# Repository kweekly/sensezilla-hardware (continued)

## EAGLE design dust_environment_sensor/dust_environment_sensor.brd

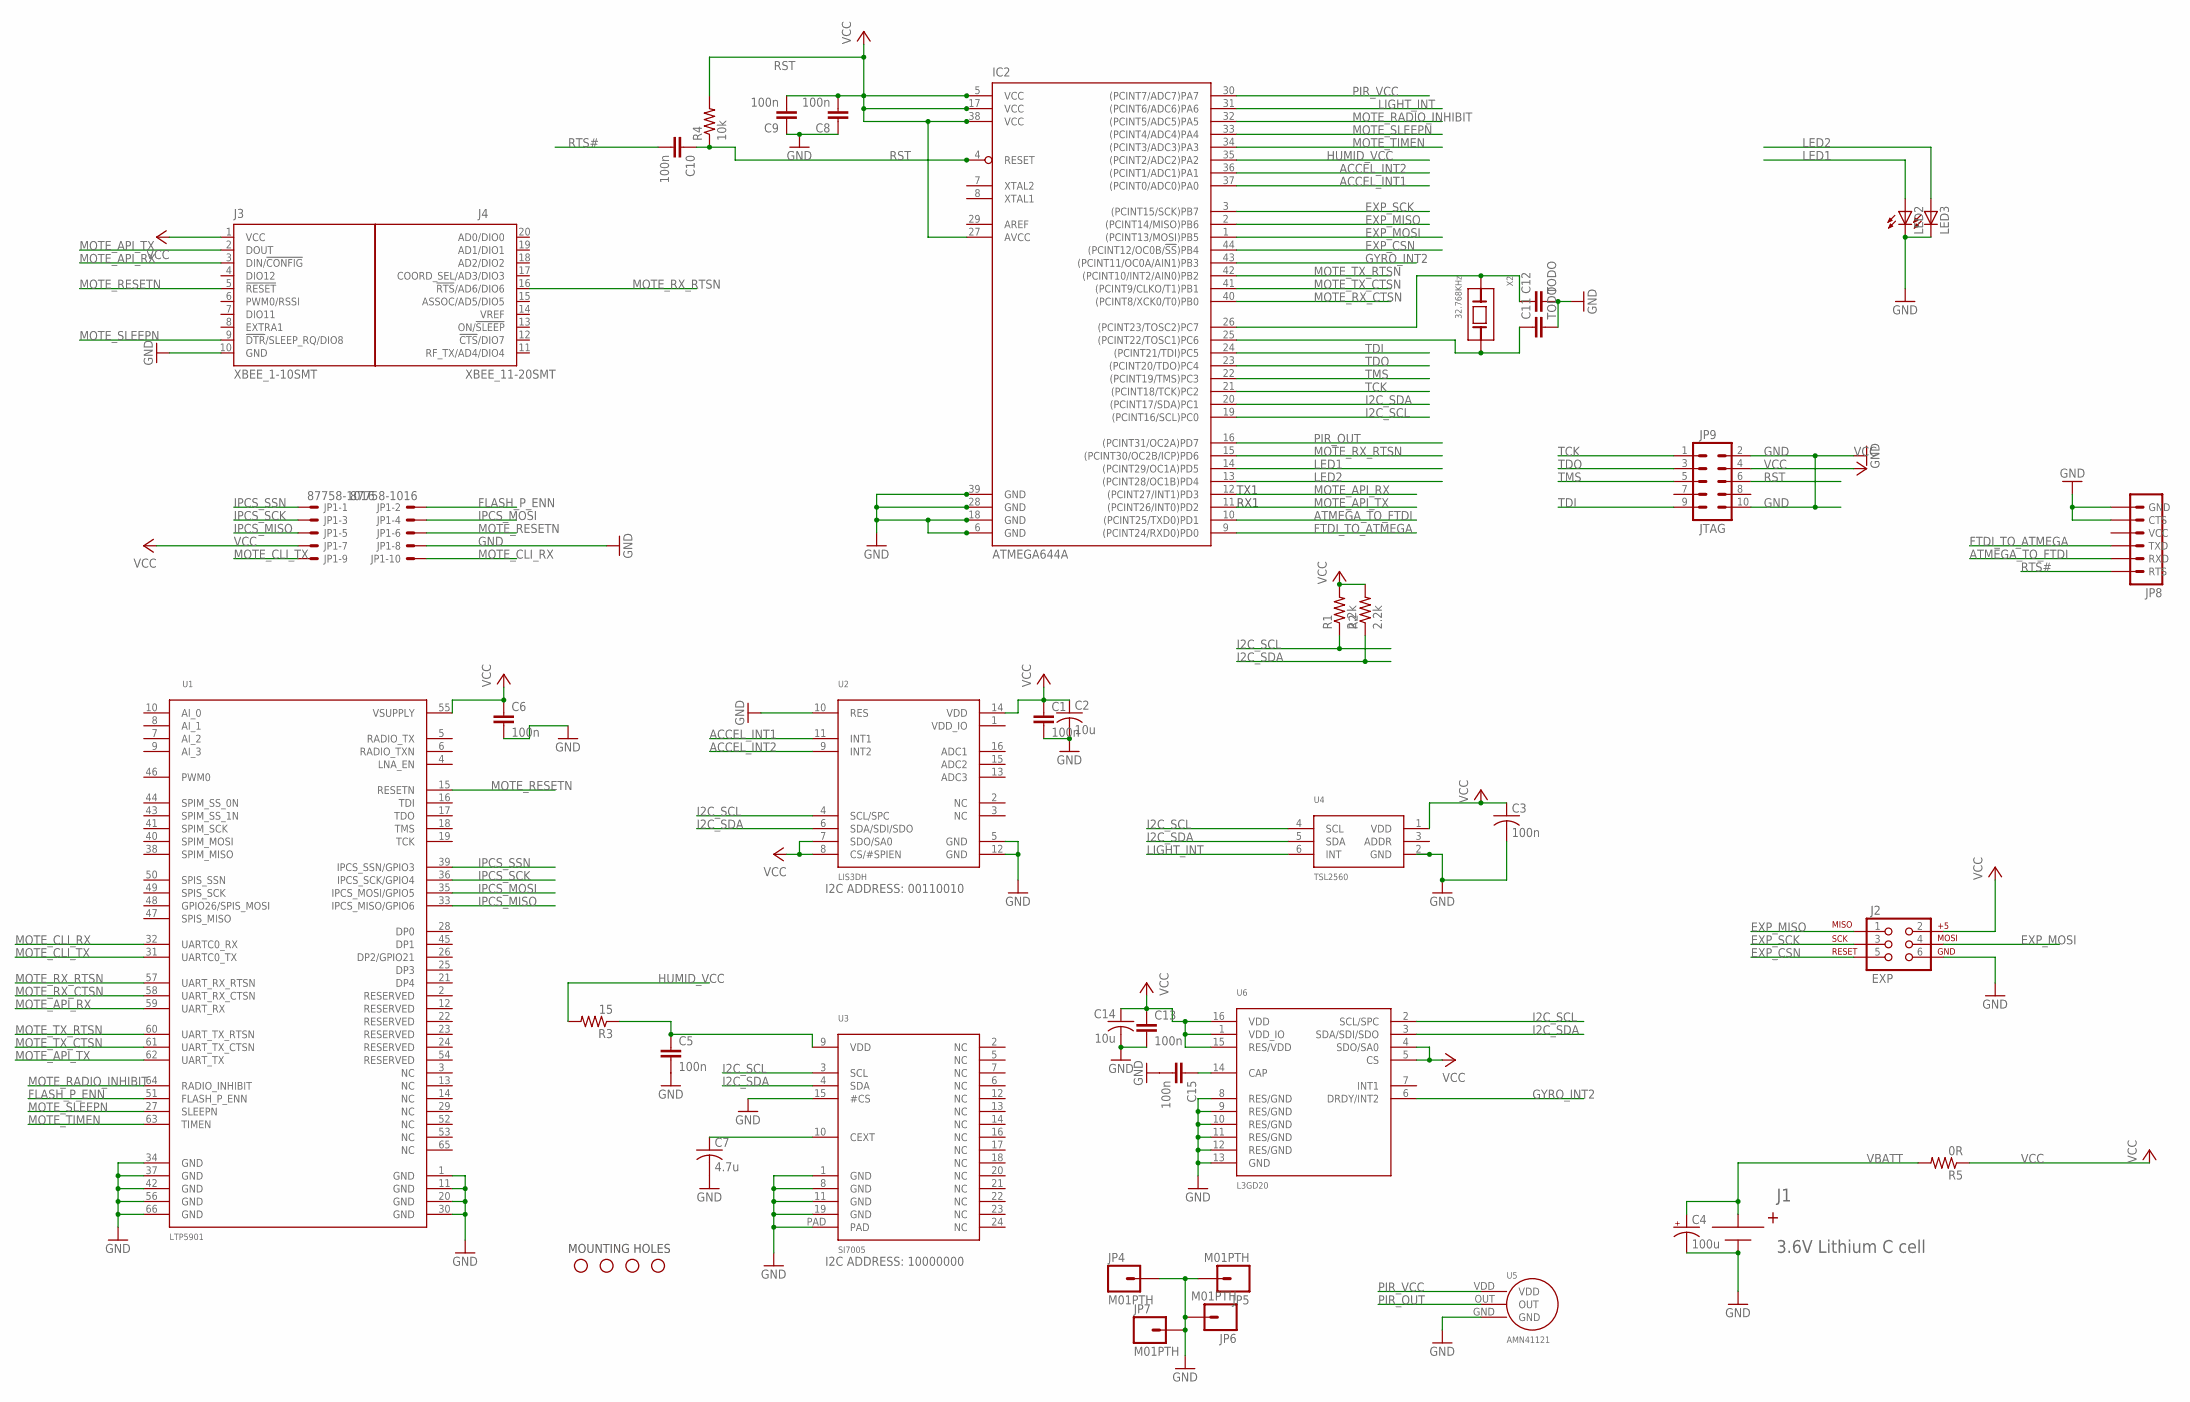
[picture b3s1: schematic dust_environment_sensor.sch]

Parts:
C1, C3, C5, C6, C8, C9, C10, C13, C15: 100n; C0603
C2, C14: 10u; C0603
C4: 100u; EIA3216-KIT
C7: 4.7u; C0603
C11, C12: TODO; C0603
IC2: ATMEGA644A; TQFP44
J1: 3.6V Lithium C cell; BX0036
J2: EXP; 2X3
J3: XBEE_1-10SMT; XBEE_1-10_SMT
J4: XBEE_11-20SMT; XBEE_11-20_SMT
JP1: 87758-1016
JP4, JP5, JP6, JP7: M01PTH; 1X01
JP8: FTDI_CABLESIP; 1X06
JP9: JTAG; AVR_ICSP
LED2, LED3: LEDCHIPLED_0805; CHIPLED_0805
R1, R2: 2.2k; R0603
R3: 15; R0603
R4: 10k; R0603
R5: 0R; R0603
STANDOFF1, STANDOFF2, STANDOFF3, STANDOFF4: STAND-OFF
U1: LTP5901; LTP5901_MODULE
U2: LIS3DH; LGA16_ST
U3: SI7005; QFN24_SILICON_LABS
U4: TSL2560; CL6_TAOS
U5: AMN41121
U6: L3GD20; LGA16_4X4_ST
X2: 32.768KHz; ABS07

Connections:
ACCEL_INT1: IC2.37 ((PCINT0/ADC0)PA0), U2.11 (INT1)
ACCEL_INT2: IC2.36 ((PCINT1/ADC1)PA1), U2.9 (INT2)
ATMEGA_TO_FTDI: IC2.10 ((PCINT25/TXD0)PD1), JP8.5 (RXD)
EXP_CSN: IC2.44 ((PCINT12/OC0B/!SS!)PB4), J2.5
EXP_MISO: IC2.2 ((PCINT14/MISO)PB6), J2.1
EXP_MOSI: IC2.1 ((PCINT13/MOSI)PB5), J2.4
EXP_SCK: IC2.3 ((PCINT15/SCK)PB7), J2.3
FLASH_P_ENN: JP1.2, U1.51 (FLASH_P_ENN)
FTDI_TO_ATMEGA: IC2.9 ((PCINT24/RXD0)PD0), JP8.4 (TXD)
GND: C1.2, C2.2, C3.2, C4.C (-), C5.2, C6.2, C7.2, C8.1, C9.1, C11.2, C12.2, C13.2, C14.2, C15.2, IC2.6 (GND), IC2.18 (GND), IC2.28 (GND), IC2.39 (GND), J1.NEG, J2.6, J3.10 (GND), JP1.8, JP4.1, JP5.1, JP6.1, JP7.1, JP8.1 (GND), JP8.2 (CTS), JP9.2, JP9.10, LED2.C, LED3.C, U1.1 (GND), U1.11 (GND), U1.20 (GND), U1.30 (GND), U1.34 (GND), U1.37 (GND), U1.42 (GND), U1.56 (GND), U1.66 (GND), U2.5 (GND), U2.10 (RES), U2.12 (GND), U3.1 (GND), U3.8 (GND), U3.11 (GND), U3.15 (#CS), U3.19 (GND), U3.PAD, U4.2 (GND), U5.GND, U6.8 (RES/GND), U6.9 (RES/GND), U6.10 (RES/GND), U6.11 (RES/GND), U6.12 (RES/GND), U6.13 (GND)
GYRO_INT2: IC2.43 ((PCINT11/OC0A/AIN1)PB3), U6.6 (DRDY/INT2)
HUMID_VCC: IC2.35 ((PCINT2/ADC2)PA2), R3.2
I2C_SCL: IC2.19 ((PCINT16/SCL)PC0), R1.1, U2.4 (SCL/SPC), U3.3 (SCL), U4.4 (SCL), U6.2 (SCL/SPC)
I2C_SDA: IC2.20 ((PCINT17/SDA)PC1), R2.1, U2.6 (SDA/SDI/SDO), U3.4 (SDA), U4.5 (SDA), U6.3 (SDA/SDI/SDO)
IPCS_MISO: JP1.5, U1.33 (IPCS_MISO/GPIO6)
IPCS_MOSI: JP1.4, U1.35 (IPCS_MOSI/GPIO5)
IPCS_SCK: JP1.3, U1.36 (IPCS_SCK/GPIO4)
IPCS_SSN: JP1.1, U1.39 (IPCS_SSN/GPIO3)
LED1: IC2.14 ((PCINT29/OC1A)PD5), LED2.A
LED2: IC2.13 ((PCINT28/OC1B)PD4), LED3.A
LIGHT_INT: IC2.31 ((PCINT6/ADC6)PA6), U4.6 (INT)
MOTE_API_RX: IC2.12 ((PCINT27/INT1)PD3), J3.3 (DIN/!CONFIG), U1.59 (UART_RX)
MOTE_API_TX: IC2.11 ((PCINT26/INT0)PD2), J3.2 (DOUT), U1.62 (UART_TX)
MOTE_CLI_RX: JP1.10, U1.32 (UARTC0_RX)
MOTE_CLI_TX: JP1.9, U1.31 (UARTC0_TX)
MOTE_RADIO_INHIBIT: IC2.32 ((PCINT5/ADC5)PA5), U1.64 (RADIO_INHIBIT)
MOTE_RESETN: J3.5 (!RESET), JP1.6, U1.15 (RESETN)
MOTE_RX_CTSN: IC2.40 ((PCINT8/XCK0/T0)PB0), U1.58 (UART_RX_CTSN)
MOTE_RX_RTSN: IC2.15 ((PCINT30/OC2B/ICP)PD6), J4.16 (!RTS!/AD6/DIO6), U1.57 (UART_RX_RTSN)
MOTE_SLEEPN: IC2.33 ((PCINT4/ADC4)PA4), J3.9 (!DTR!/SLEEP_RQ/DIO8), U1.27 (SLEEPN)
MOTE_TIMEN: IC2.34 ((PCINT3/ADC3)PA3), U1.63 (TIMEN)
MOTE_TX_CTSN: IC2.41 ((PCINT9/CLKO/T1)PB1), U1.61 (UART_TX_CTSN)
MOTE_TX_RTSN: IC2.42 ((PCINT10/INT2/AIN0)PB2), U1.60 (UART_TX_RTSN)
unnamed: C7.1, U3.10 (CEXT)
unnamed: C15.1, U6.14 (CAP)
unnamed: C5.1, R3.1, U3.9 (VDD)
unnamed: C11.1, IC2.25 ((PCINT22/TOSC1)PC6), X2.2 (B)
unnamed: C12.1, IC2.26 ((PCINT23/TOSC2)PC7), X2.1 (A)
PIR_OUT: IC2.16 ((PCINT31/OC2A)PD7), U5.OUT
PIR_VCC: IC2.30 ((PCINT7/ADC7)PA7), U5.VDD
RST: C10.1, IC2.4 (RESET), JP9.6, R4.1
RTS#: C10.2, JP8.6 (RTS)
TCK: IC2.21 ((PCINT18/TCK)PC2), JP9.1
TDI: IC2.24 ((PCINT21/TDI)PC5), JP9.9
TDO: IC2.23 ((PCINT20/TDO)PC4), JP9.3
TMS: IC2.22 ((PCINT19/TMS)PC3), JP9.5
VBATT: C4.A (+), J1.POS, R5.2
VCC: C1.1, C2.1, C3.1, C6.1, C8.2, C9.2, C13.1, C14.1, IC2.5 (VCC), IC2.17 (VCC), IC2.27 (AVCC), IC2.38 (VCC), J2.2, J3.1 (VCC), JP1.7, JP9.4, R1.2, R2.2, R4.2, R5.1, U1.55 (VSUPPLY), U2.7 (SDO/SA0), U2.8 (CS/#SPIEN), U2.14 (VDD), U4.1 (VDD), U6.1 (VDD_IO), U6.4 (SDO/SA0), U6.5 (CS), U6.15 (RES/VDD), U6.16 (VDD)

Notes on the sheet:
I2C ADDRESS: 00110010
MOUNTING HOLES
I2C ADDRESS: 10000000
TX1
RX1

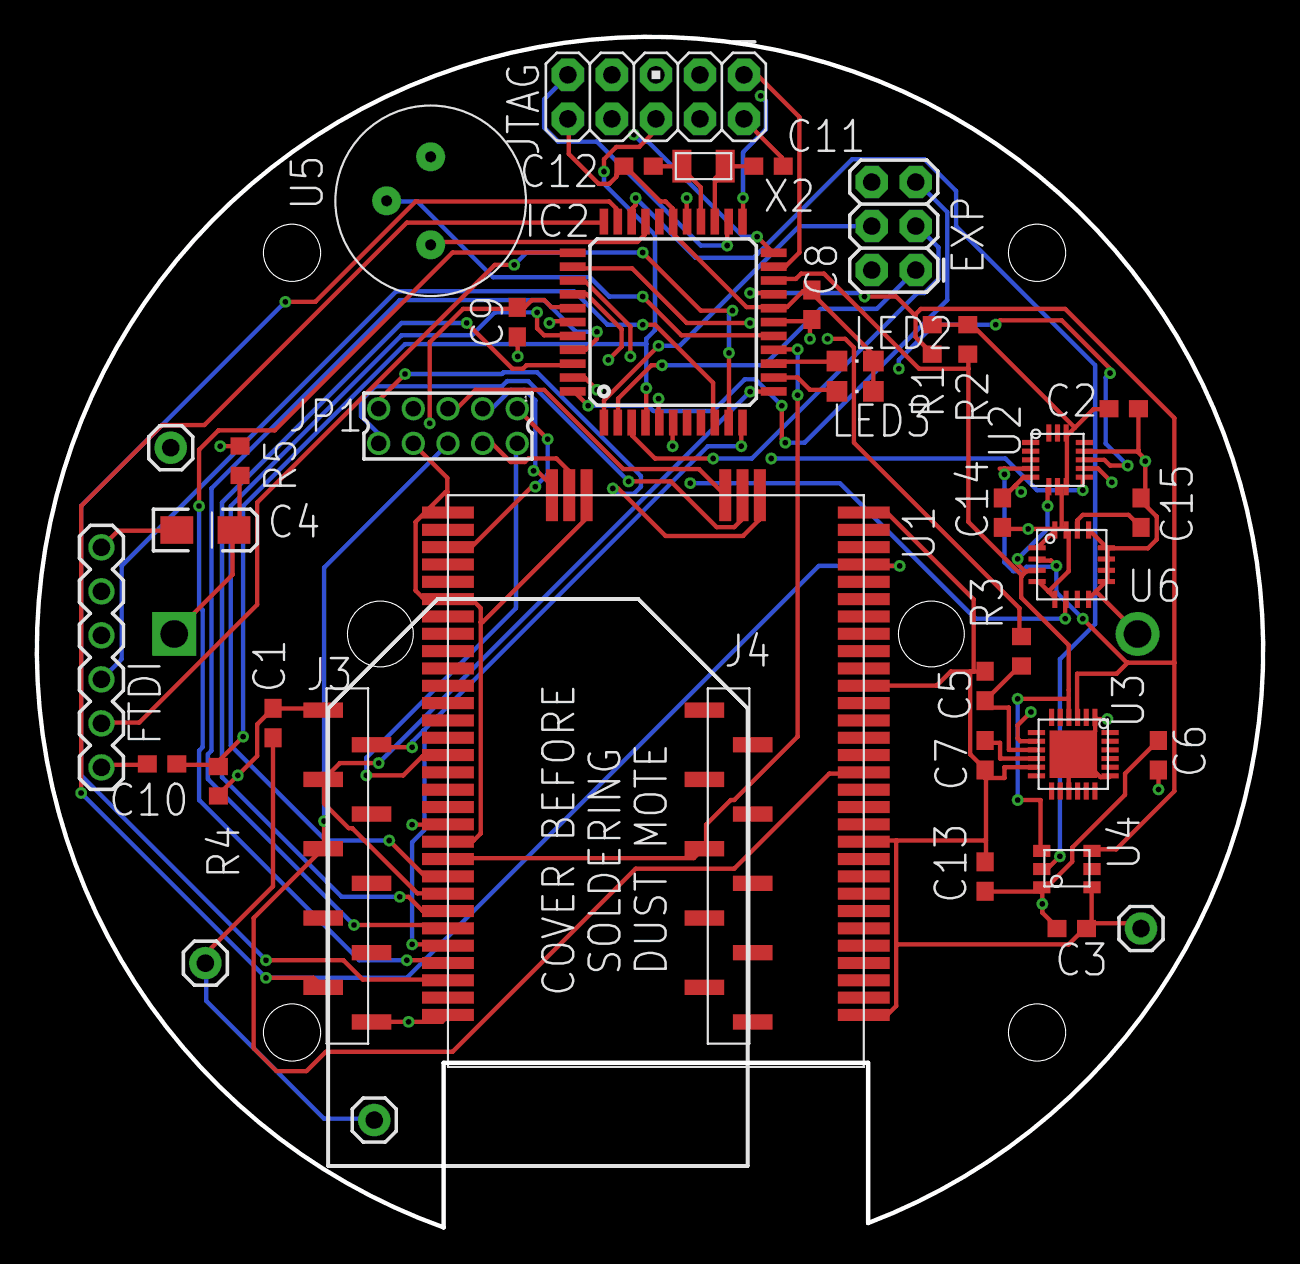
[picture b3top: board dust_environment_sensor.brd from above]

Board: 4 copper layers, 70.8 x 68.7 mm, 45 parts (1 on the bottom side), 48 nets.

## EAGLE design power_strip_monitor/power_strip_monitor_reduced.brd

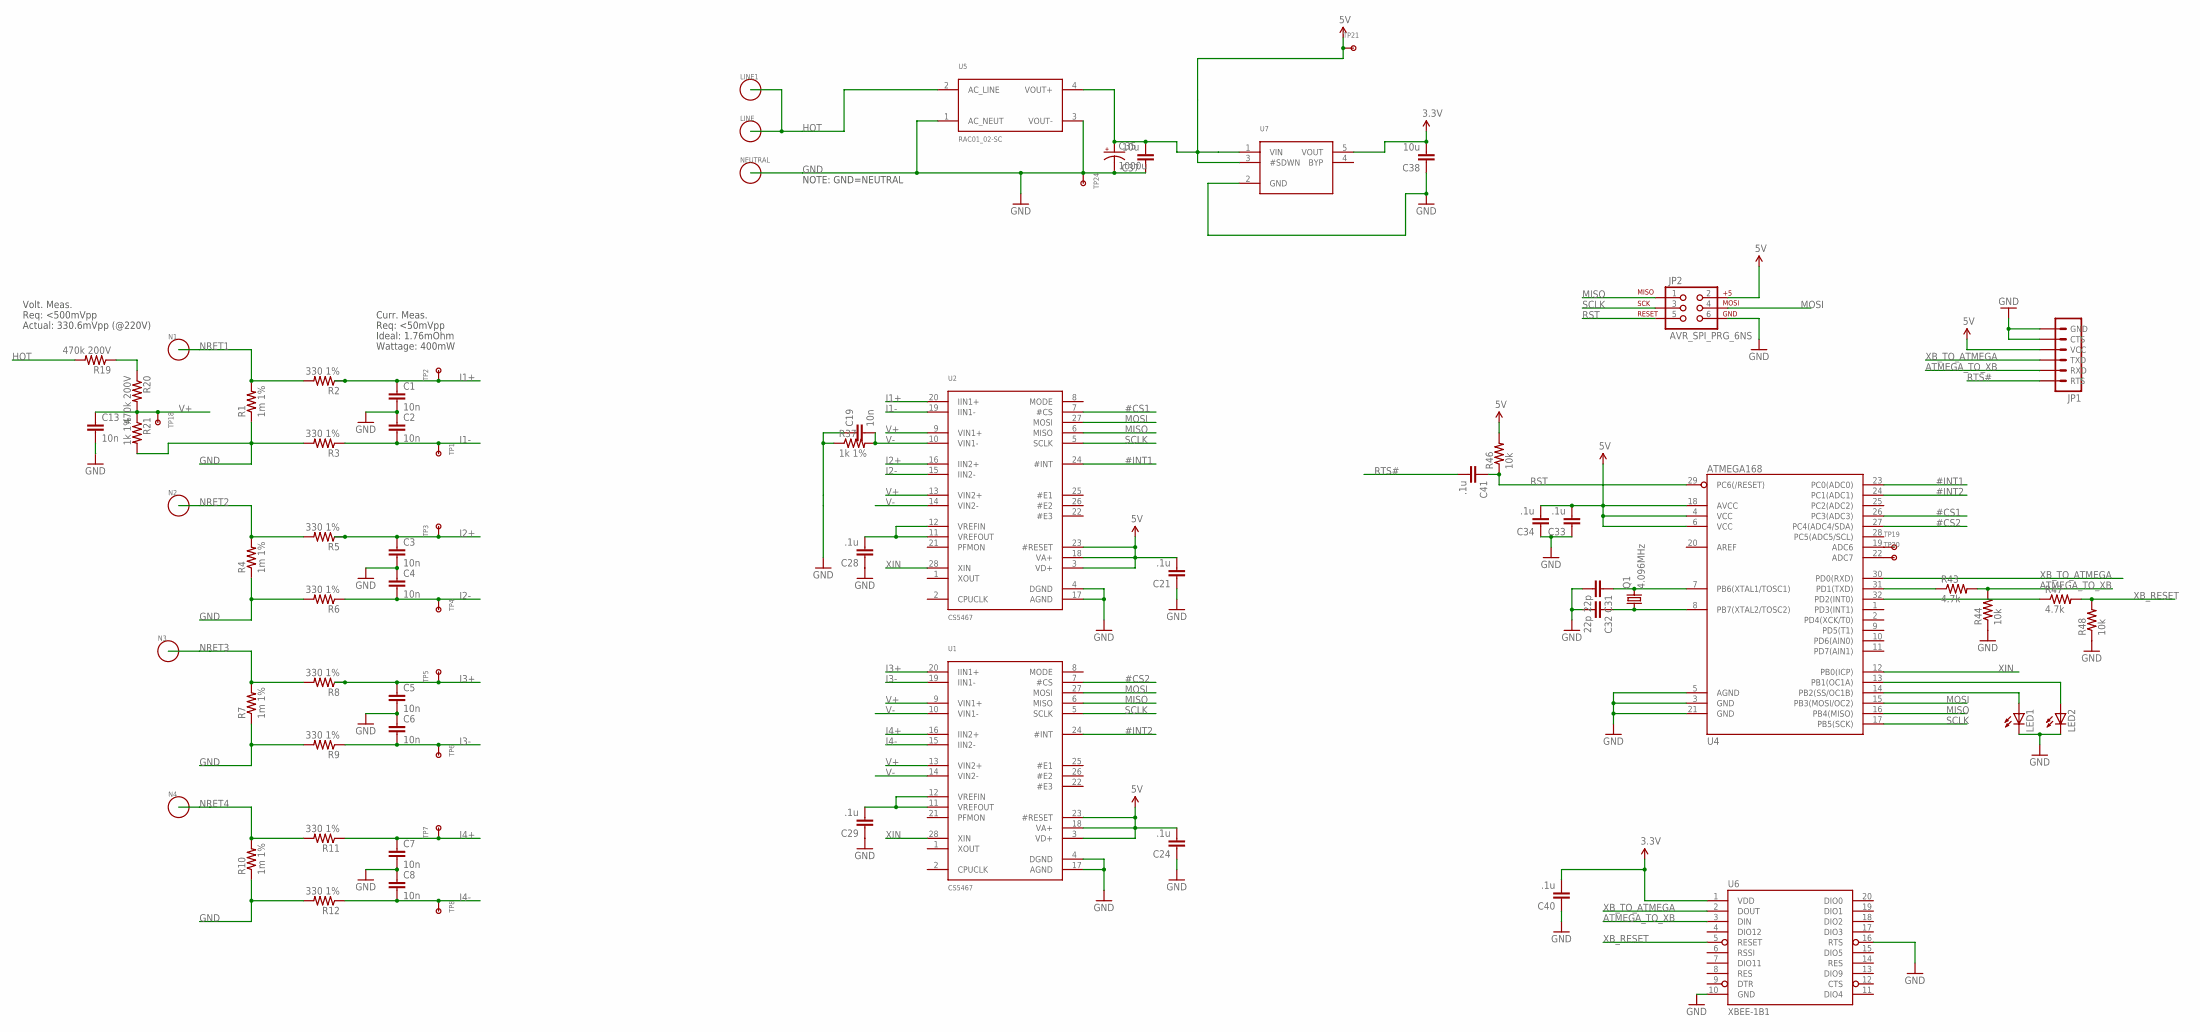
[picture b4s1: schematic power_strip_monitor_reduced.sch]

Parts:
C1, C2, C3, C4, C5, C6, C7, C8, C13, C19: 10n; 0603
C21, C24, C28, C29, C33, C34, C40, C41: .1u; 0603
C31, C32: 22p; 0603
C35: 1000u; PANASONIC_G
C37, C38: 10u; 0603
JP1: FTDI_CABLESIP; 1X06
JP2: AVR_SPI_PRG_6NS; 2X3-NS
LED1, LED2: LEDCHIPLED_0805; CHIPLED_0805
LINE, LINE1: 1P_HOLE; 14GAUGE_HOLE
N1, N2, N3, N4: 1P_HOLE; 14GAUGE_HOLE
NEUTRAL: 1P_HOLE; 14GAUGE_HOLE
Q1: 4.096MHz; HC49UP
R1, R4, R7, R10: 1m 1%; R2512
R2, R3, R5, R6, R8, R9, R11, R12: 330 1%; 0603
R19, R20: 470k 200V; 1206
R21, R37: 1k 1%; 0603
R43, R47: 4.7k; 0603
R44, R46, R48: 10k; 0603
TP1, TP2, TP3, TP4, TP5, TP6, TP7, TP8, TP18, TP19, TP20: TESTPOINTSMALLEST; TESTPOINT
TP21, TP24: TESTPOINT100MIL; TESTPOINT-100MIL
U1, U2: CS5467; SSOP28L_CIRRUS
U4: ATMEGA168; TQFP32-08
U5: RAC01_02-SC
U6: XBEE-1B1; XBEE-1
U7: LT1761-X; TSOT23-5_LINEAR

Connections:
3.3V: C38.2, C40.2, U6.1 (VDD), U7.5 (VOUT)
5V: C21.2, C24.2, C33.2, C34.2, C35.+, C37.2, JP1.3 (VCC), JP2.2, R46.2, TP21.2, U1.3 (VD+), U1.18 (VA+), U1.23 (#RESET), U2.3 (VD+), U2.18 (VA+), U2.23 (#RESET), U4.4 (VCC), U4.6 (VCC), U4.18 (AVCC), U5.4 (VOUT+), U7.1 (VIN), U7.3 (#SDWN)
#CS1: U2.7 (#CS), U4.26 (PC3(ADC3))
#CS2: U1.7 (#CS), U4.27 (PC4(ADC4/SDA))
#INT1: U2.24 (#INT), U4.23 (PC0(ADC0))
#INT2: U1.24 (#INT), U4.24 (PC1(ADC1))
ATMEGA_TO_XB: JP1.5 (RXD), R43.2, R44.2, U6.3 (DIN)
GND: C1.2, C2.1, C3.2, C4.1, C5.2, C6.1, C7.2, C8.1, C13.2, C19.1, C21.1, C24.1, C28.1, C29.1, C31.2, C32.2, C33.1, C34.1, C35.-, C37.1, C38.1, C40.1, JP1.1 (GND), JP1.2 (CTS), JP2.6, LED1.C, LED2.C, NEUTRAL.P$1, R1.1, R3.2, R4.1, R6.2, R7.1, R9.2, R10.1, R12.2, R21.2, R37.1, R44.1, R48.1, TP24.2, U1.4 (DGND), U1.17 (AGND), U2.4 (DGND), U2.17 (AGND), U4.3 (GND), U4.5 (AGND), U4.21 (GND), U5.1 (AC_NEUT), U5.3 (VOUT-), U6.10 (GND), U6.16 (RTS), U7.2 (GND)
HOT: LINE.P$1, LINE1.P$1, R19.2, U5.2 (AC_LINE)
I1+: C1.1, R2.1, TP2.P$1, U2.20 (IIN1+)
I1-: C2.2, R3.1, TP1.P$1, U2.19 (IIN1-)
I2+: C3.1, R5.1, TP3.P$1, U2.16 (IIN2+)
I2-: C4.2, R6.1, TP4.P$1, U2.15 (IIN2-)
I3+: C5.1, R8.1, TP5.P$1, U1.20 (IIN1+)
I3-: C6.2, R9.1, TP6.P$1, U1.19 (IIN1-)
I4+: C7.1, R11.1, TP7.P$1, U1.16 (IIN2+)
I4-: C8.2, R12.1, TP8.P$1, U1.15 (IIN2-)
MISO: JP2.1, U1.6 (MISO), U2.6 (MISO), U4.16 (PB4(MISO))
MOSI: JP2.4, U1.27 (MOSI), U2.27 (MOSI), U4.15 (PB3(MOSI/OC2))
unnamed: LED2.A, U4.13 (PB1(OC1A))
unnamed: R19.1, R20.1
unnamed: LED1.A, U4.14 (PB2(SS/OC1B))
unnamed: C29.2, U1.11 (VREFOUT), U1.12 (VREFIN)
unnamed: C28.2, U2.11 (VREFOUT), U2.12 (VREFIN)
unnamed: C31.1, Q1.2, U4.7 (PB6(XTAL1/TOSC1))
unnamed: C32.1, Q1.1, U4.8 (PB7(XTAL2/TOSC2))
unnamed: TP19.P$1, U4.19 (ADC6)
unnamed: TP20.P$1, U4.22 (ADC7)
unnamed: R43.1, U4.31 (PD1(TXD))
unnamed: R47.1, U4.32 (PD2(INT0))
NRET1: N1.P$1, R1.2, R2.2
NRET2: N2.P$1, R4.2, R5.2
NRET3: N3.P$1, R7.2, R8.2
NRET4: N4.P$1, R10.2, R11.2
RST: C41.1, JP2.5, R46.1, U4.29 (PC6(/RESET))
RTS#: C41.2, JP1.6 (RTS)
SCLK: JP2.3, U1.5 (SCLK), U2.5 (SCLK), U4.17 (PB5(SCK))
V+: C13.1, R20.2, R21.1, TP18.P$1, U1.9 (VIN1+), U1.13 (VIN2+), U2.9 (VIN1+), U2.13 (VIN2+)
V-: C19.2, R37.2, U1.10 (VIN1-), U1.14 (VIN2-), U2.10 (VIN1-), U2.14 (VIN2-)
XB_RESET: R47.2, R48.2, U6.5 (RESET)
XB_TO_ATMEGA: JP1.4 (TXD), U4.30 (PD0(RXD)), U6.2 (DOUT)
XIN: U1.28 (XIN), U2.28 (XIN), U4.12 (PB0(ICP))

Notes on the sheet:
Req: <500mVpp
Actual: 330.6mVpp (@220V)
Volt. Meas.
Curr. Meas.
Req: <50mVpp
Ideal: 1.76mOhm
Wattage: 400mW
NOTE: GND=NEUTRAL

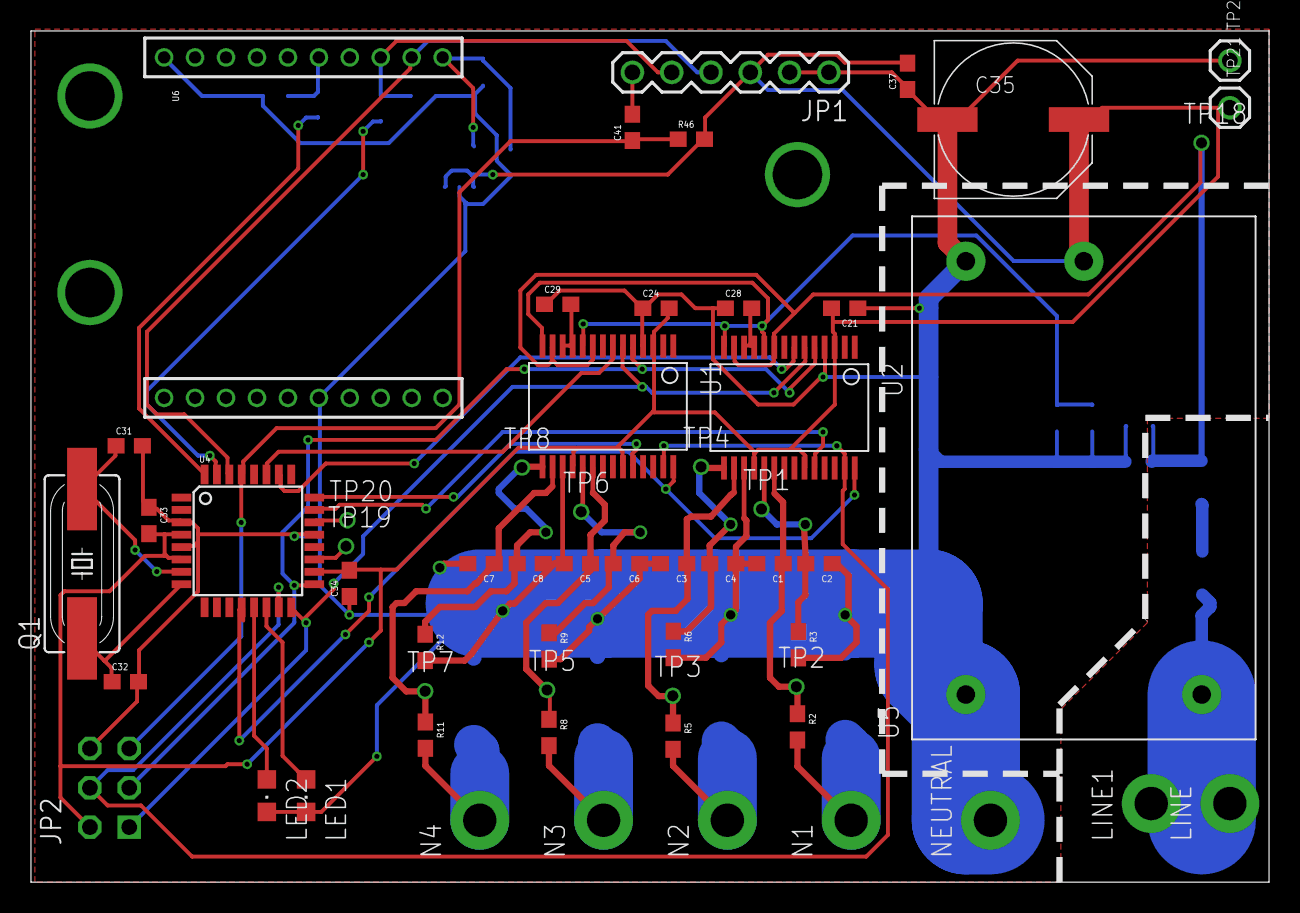
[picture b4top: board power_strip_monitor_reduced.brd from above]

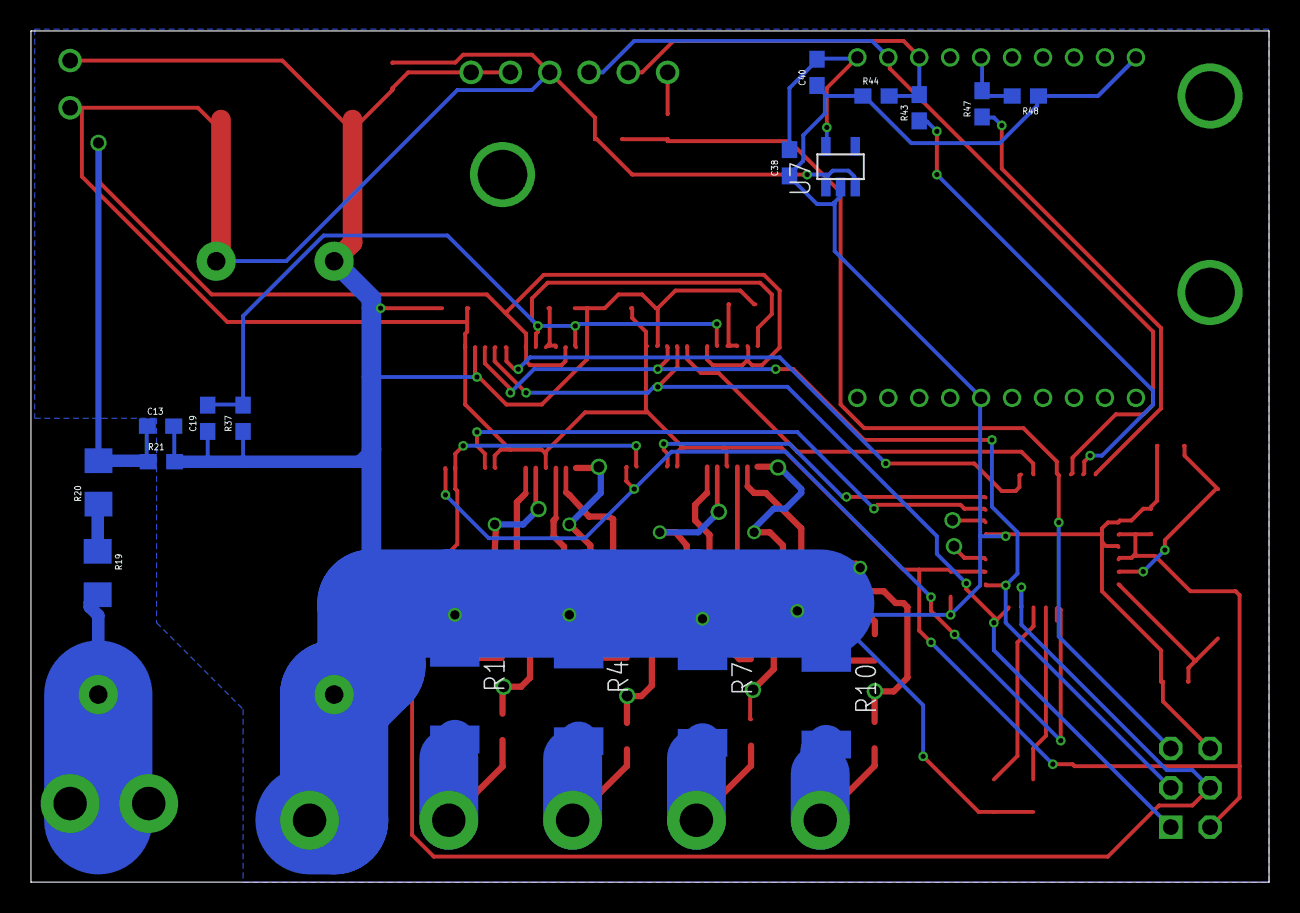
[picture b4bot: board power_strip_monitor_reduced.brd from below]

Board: 2 copper layers, 80.0 x 55.0 mm, 75 parts (17 on the bottom side), 42 nets.

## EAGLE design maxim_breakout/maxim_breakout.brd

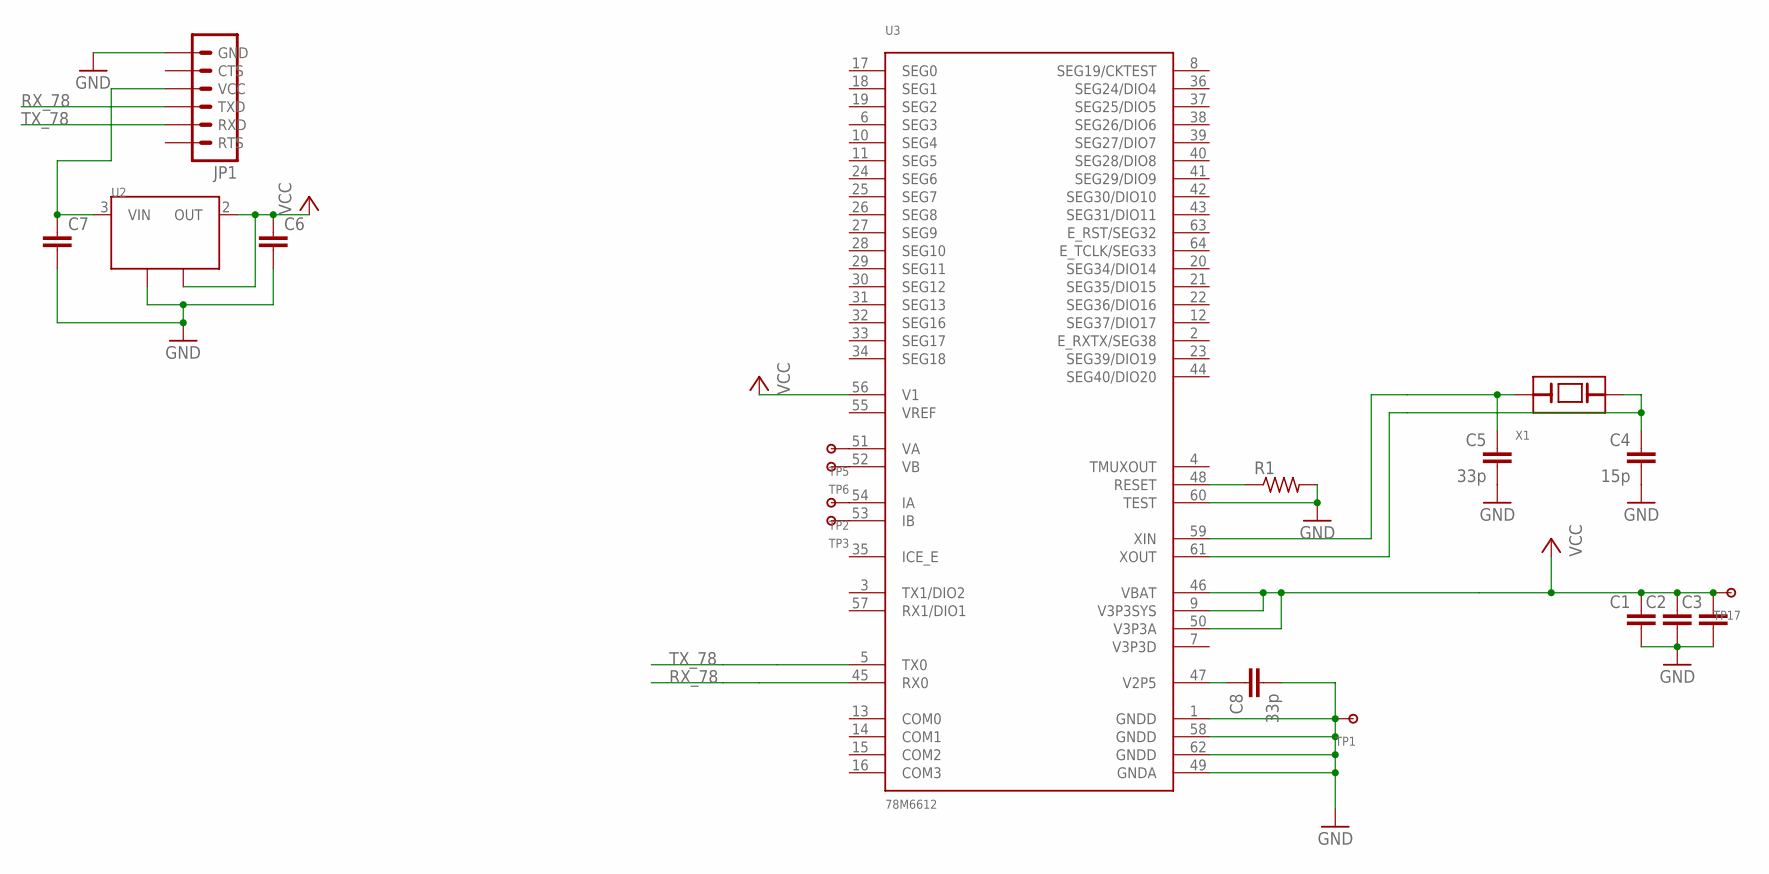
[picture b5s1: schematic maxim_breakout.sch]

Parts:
C1, C2, C3, C6, C7: CAP0805; 0805
C4: 15p; 0805
C5, C8: 33p; 0805
JP1: FTDI_CABLELOCK_LONGPADS; 1X06_LOCK_LONGPADS
R1: R-US_R0805; R0805
TP1, TP2, TP3, TP5, TP6, TP17: TESTPOINT100MIL; TESTPOINT-100MIL
U2: NX1117C; SOT223
U3: 78M6612
X1: XTALABS07; ABS07

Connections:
GND: C1.2, C2.2, C3.2, C4.2, C5.2, C6.2, C7.2, C8.2, JP1.1 (GND), R1.2, TP1.2, U2.1 (GND), U3.1 (GNDD), U3.49 (GNDA), U3.58 (GNDD), U3.60 (TEST), U3.62 (GNDD)
unnamed: C7.1, JP1.3 (VCC), U2.3 (VIN)
unnamed: R1.1, U3.48 (RESET)
unnamed: C8.1, U3.47 (V2P5)
unnamed: TP2.2, U3.54 (IA)
unnamed: TP3.2, U3.53 (IB)
unnamed: TP5.2, U3.51 (VA)
unnamed: TP6.2, U3.52 (VB)
unnamed: C4.1, U3.61 (XOUT), X1.2 (B)
unnamed: C5.1, U3.59 (XIN), X1.1 (A)
RX_78: JP1.4 (TXD), U3.45 (RX0)
TX_78: JP1.5 (RXD), U3.5 (TX0)
VCC: C1.1, C2.1, C3.1, C6.1, TP17.2, U2.2 (OUT), U2.4 (TAB), U3.9 (V3P3SYS), U3.46 (VBAT), U3.50 (V3P3A), U3.56 (V1)

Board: 2 copper layers, 19 parts (0 on the bottom side), 13 nets, no tracks yet.

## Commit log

2012-07-14 Update master
2012-07-26 Added preliminary schematics for power supply and measuring.
2012-08-01 Added ground/supply connections.
2012-08-04 Kevin's working on the board
2012-08-13 Finished schematic, starting component selection
2012-08-13 Finding more parts
2012-08-14 Saving power supply changes
2012-08-14 Parts identified, new power supply
2012-08-15 reduced power strip monitor laid out
2012-08-15 Board laid out, parts found
2012-08-17 Added LEDs on schematic and layout
2012-08-17 remove soldermask on power traces
2012-08-17 Added DRC rules, second LINE hole
2012-08-31 Added plastic mount
2012-12-07 Added Linear mote to libraryt
2012-12-10 More library adjustments
2012-12-10 Dust environ sensor
2012-12-11 Putting together dust sensor mote
2012-12-11 Battery holder
2012-12-12 more work on dust sensor
2012-12-13 BOM done
2013-01-18 Added new version of power strip
2013-01-19 Finished, now optimize
2013-01-19 components placed
2013-01-19 Trying to route now
2013-01-31 Latest Powerstrip changes
2013-01-31 eMachineShop file
2013-02-01 Ready to route
2013-02-01 ready for mfg? BOM needs fixing
2013-02-01 Latest powerstrip enclosure
2013-02-05 BOM Updates
2013-02-21 Latest changes
2013-03-15 added some datasheets and pictures
2013-03-28 Adding version 2 of dust env. sensor
2013-04-12 changes for v2
2013-04-12 rename BOM
2013-04-12 Test golden version of ES2
2013-05-14 added enclosure
2013-05-15 Enclosure fixes
2013-06-19 enclosure fits quite nicely
2013-09-24 added a bunch of 3d models
2013-10-22 V3 added for quotation
2013-10-22 tiny DES3
2013-10-22 schematic and placement done?
2013-10-23 boards submitted to fab
2013-11-20 latest updates before revision
2013-11-20 Updated board design and shipping
2013-11-26 added some enclosures that didn't get added earlier
